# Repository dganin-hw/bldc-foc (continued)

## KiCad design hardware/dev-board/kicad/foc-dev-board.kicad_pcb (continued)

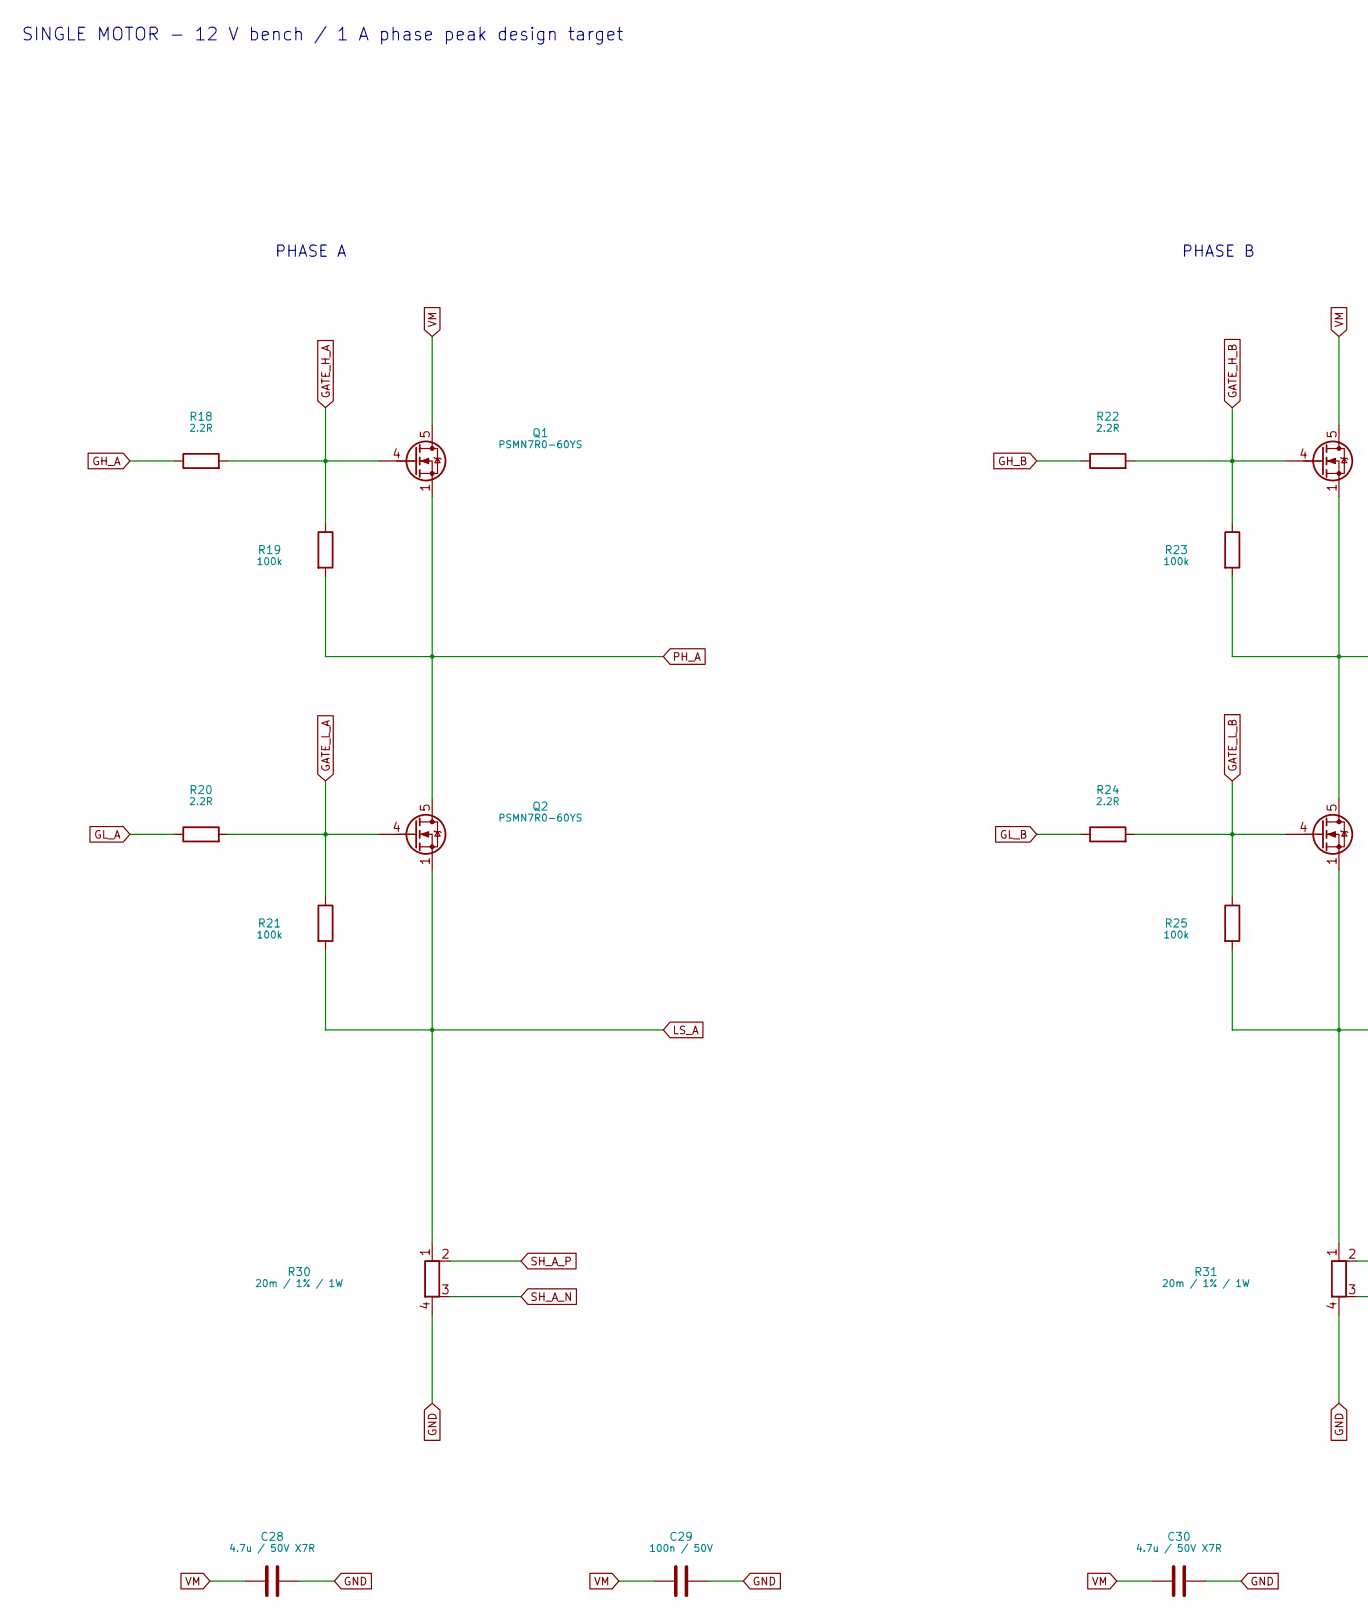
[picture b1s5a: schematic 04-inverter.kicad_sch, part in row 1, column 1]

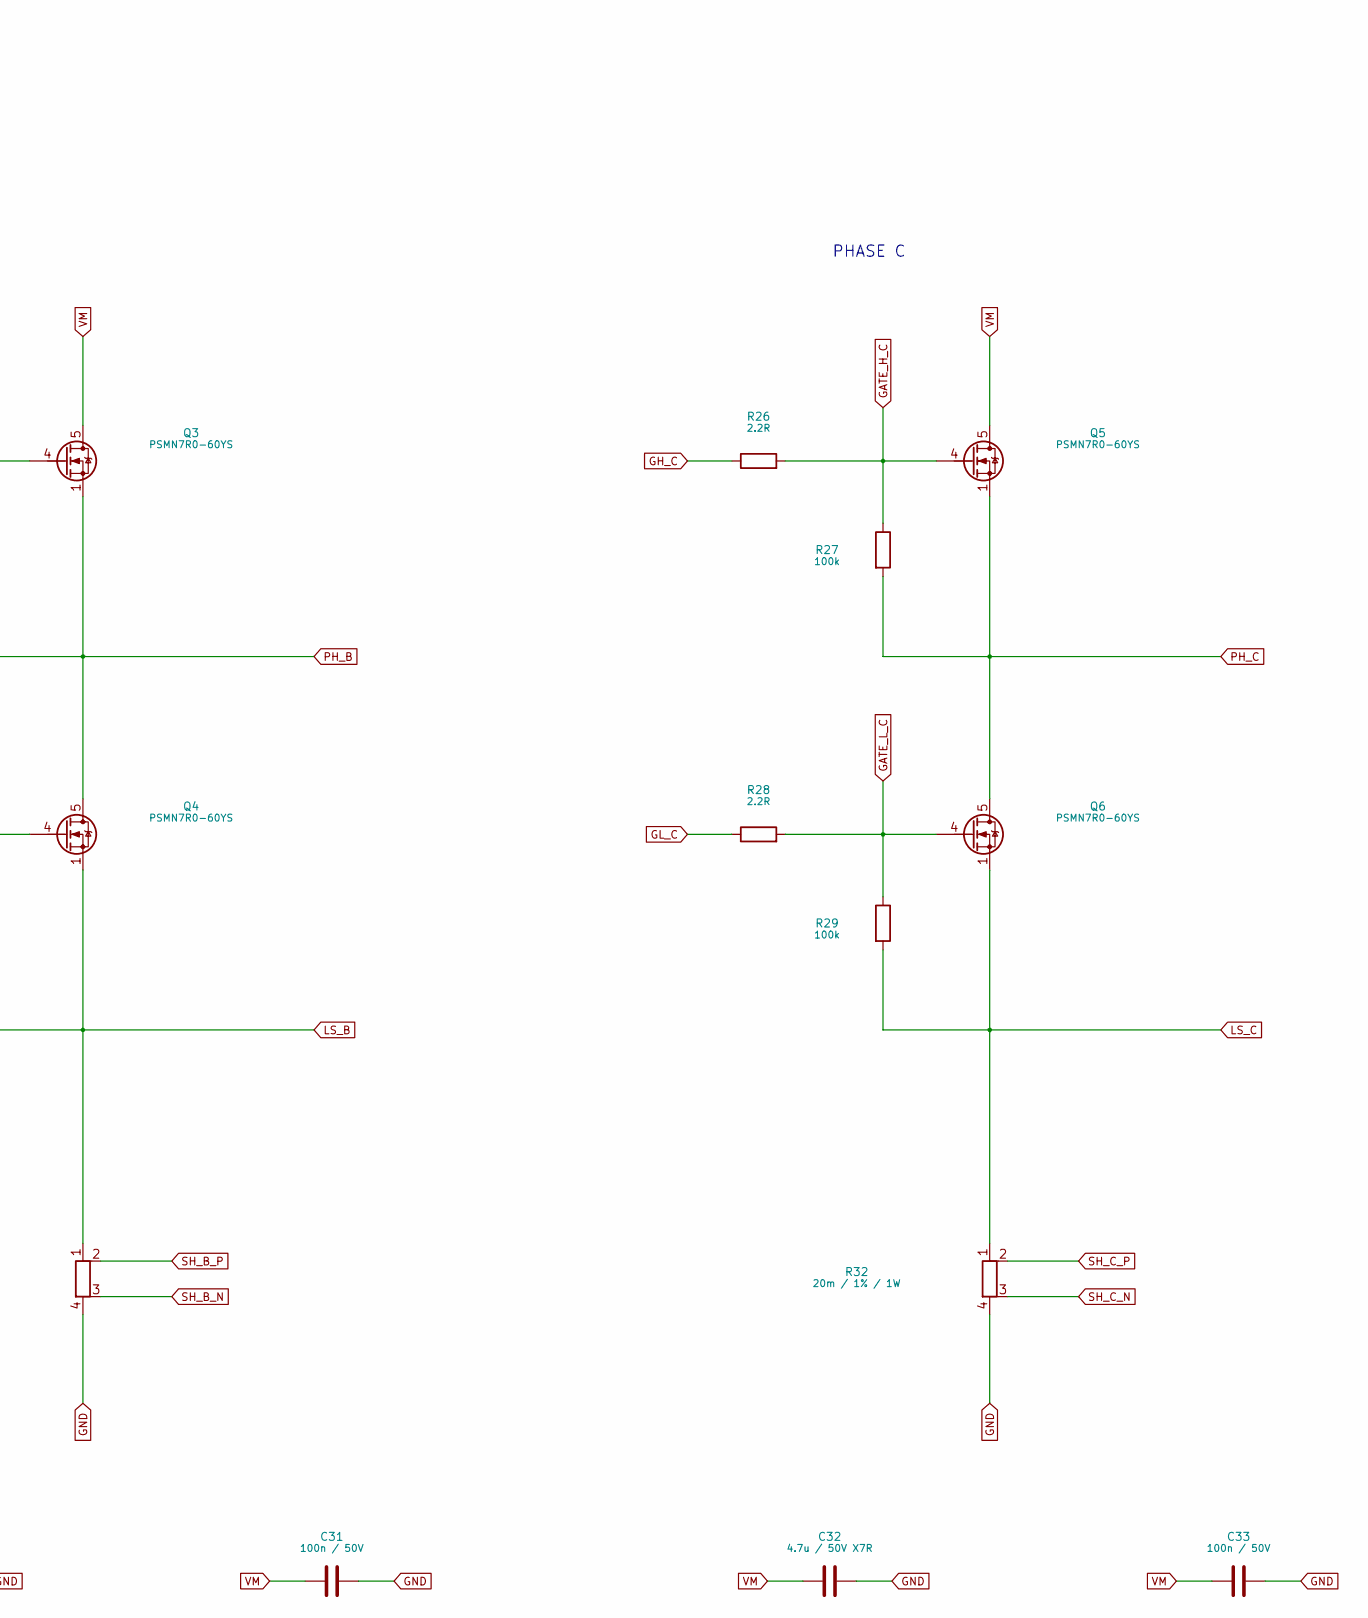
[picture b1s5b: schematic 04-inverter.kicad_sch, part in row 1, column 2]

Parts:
C28, C30, C32: 4.7u / 50V X7R; C_1210_3225Metric
C29, C31, C33: 100n / 50V; C_0603_1608Metric
Q1, Q2, Q3, Q4, Q5, Q6: PSMN7R0-60YS; LFPAK56; MPN PSMN7R0-60YS,115
R18, R20, R22, R24, R26, R28: 2.2R; R_0603_1608Metric
R19, R21, R23, R25, R27, R29: 100k; R_0603_1608Metric
R30, R31, R32: 20m / 1% / 1W; R_Shunt_Vishay_WSK2512_6332Metric_T1.19mm; MPN WSK2512R0200FEA

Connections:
GATE_H_A: Q1.4 (G), R18.2, R19.1; also elsewhere on the board
GATE_H_B: Q3.4 (G), R22.2, R23.1; also elsewhere on the board
GATE_H_C: Q5.4 (G), R26.2, R27.1; also elsewhere on the board
GATE_L_A: Q2.4 (G), R20.2, R21.1; also elsewhere on the board
GATE_L_B: Q4.4 (G), R24.2, R25.1; also elsewhere on the board
GATE_L_C: Q6.4 (G), R28.2, R29.1; also elsewhere on the board
GH_A: R18.1; also elsewhere on the board
GH_B: R22.1; also elsewhere on the board
GH_C: R26.1; also elsewhere on the board
GL_A: R20.1; also elsewhere on the board
GL_B: R24.1; also elsewhere on the board
GL_C: R28.1; also elsewhere on the board
GND: C28.2, C29.2, C30.2, C31.2, C32.2, C33.2, R30.4, R31.4, R32.4; also elsewhere on the board
LS_A: Q2.1 (S), Q2.2 (S), Q2.3 (S), R21.2, R30.1; also elsewhere on the board
LS_B: Q4.1 (S), Q4.2 (S), Q4.3 (S), R25.2, R31.1; also elsewhere on the board
LS_C: Q6.1 (S), Q6.2 (S), Q6.3 (S), R29.2, R32.1; also elsewhere on the board
PH_A: Q1.1 (S), Q1.2 (S), Q1.3 (S), Q2.5 (D), R19.2; also elsewhere on the board
PH_B: Q3.1 (S), Q3.2 (S), Q3.3 (S), Q4.5 (D), R23.2; also elsewhere on the board
PH_C: Q5.1 (S), Q5.2 (S), Q5.3 (S), Q6.5 (D), R27.2; also elsewhere on the board
SH_A_N: R30.3; also elsewhere on the board
SH_A_P: R30.2; also elsewhere on the board
SH_B_N: R31.3; also elsewhere on the board
SH_B_P: R31.2; also elsewhere on the board
SH_C_N: R32.3; also elsewhere on the board
SH_C_P: R32.2; also elsewhere on the board
VM: C28.1, C29.1, C30.1, C31.1, C32.1, C33.1, Q1.5 (D), Q3.5 (D), Q5.5 (D); also elsewhere on the board

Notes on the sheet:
PHASE B
PHASE A
SINGLE MOTOR - 12 V bench / 1 A phase peak design target
PHASE C

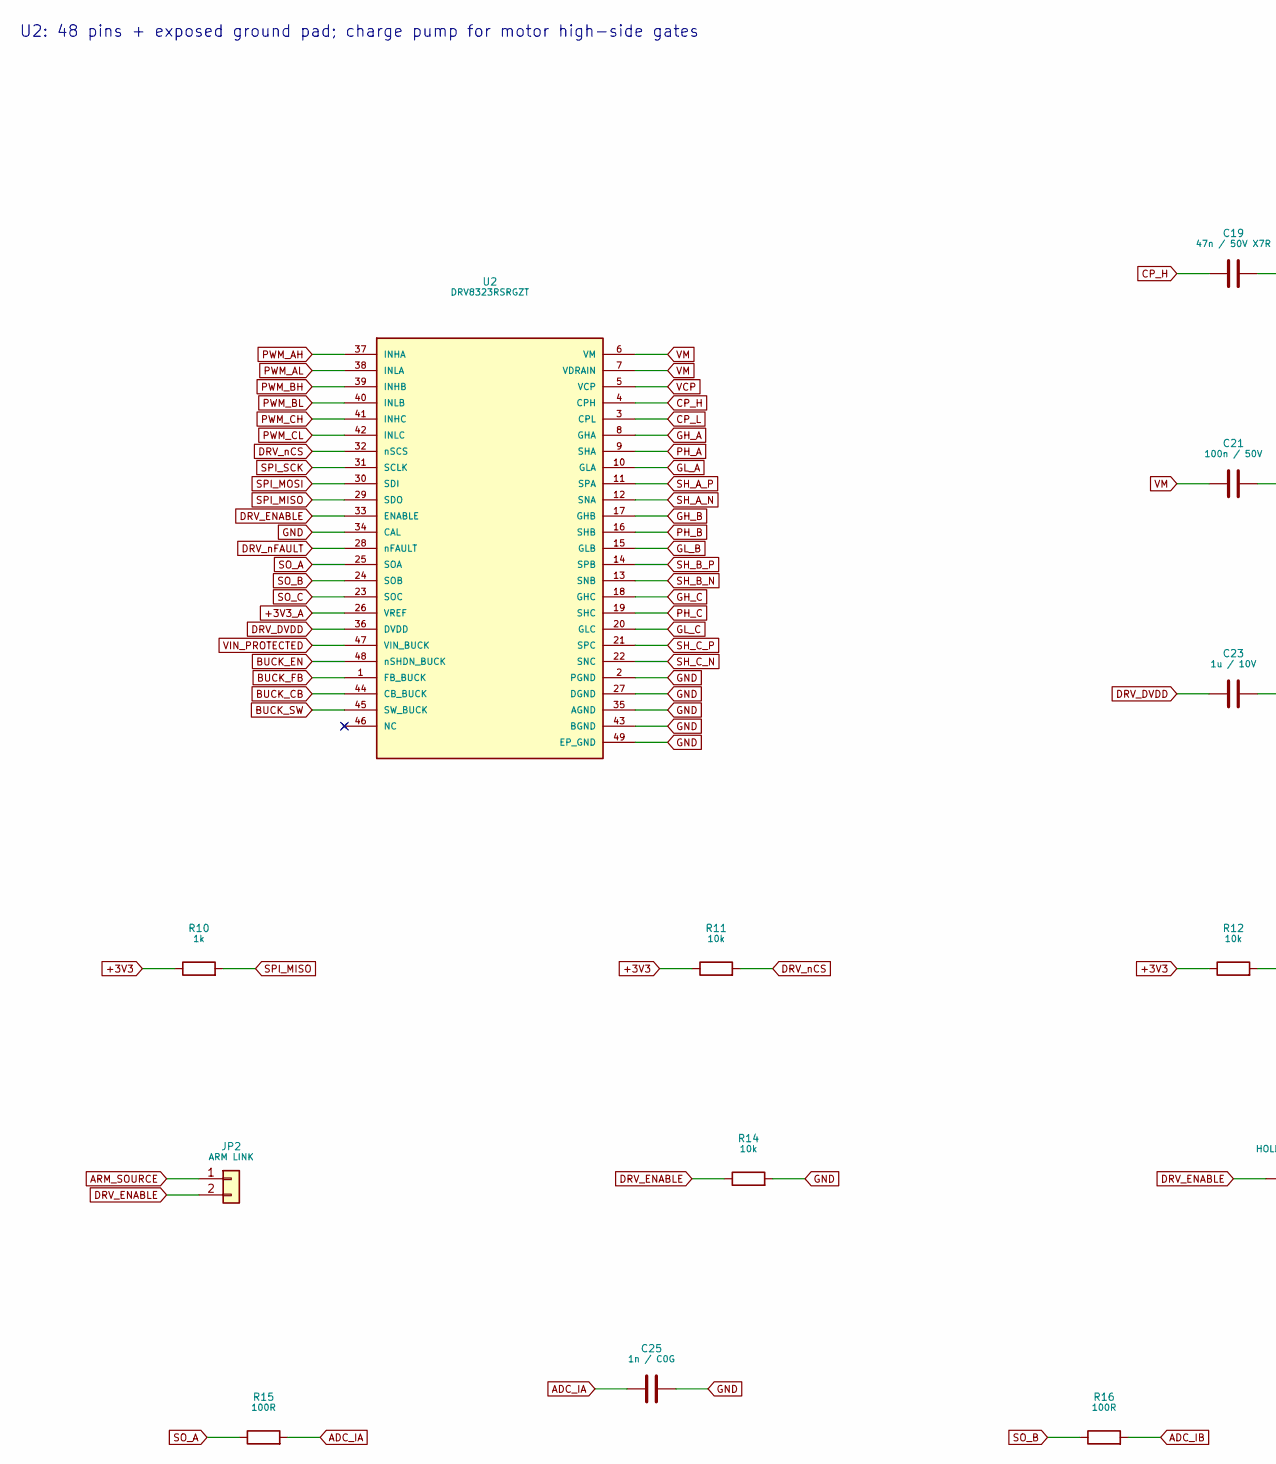
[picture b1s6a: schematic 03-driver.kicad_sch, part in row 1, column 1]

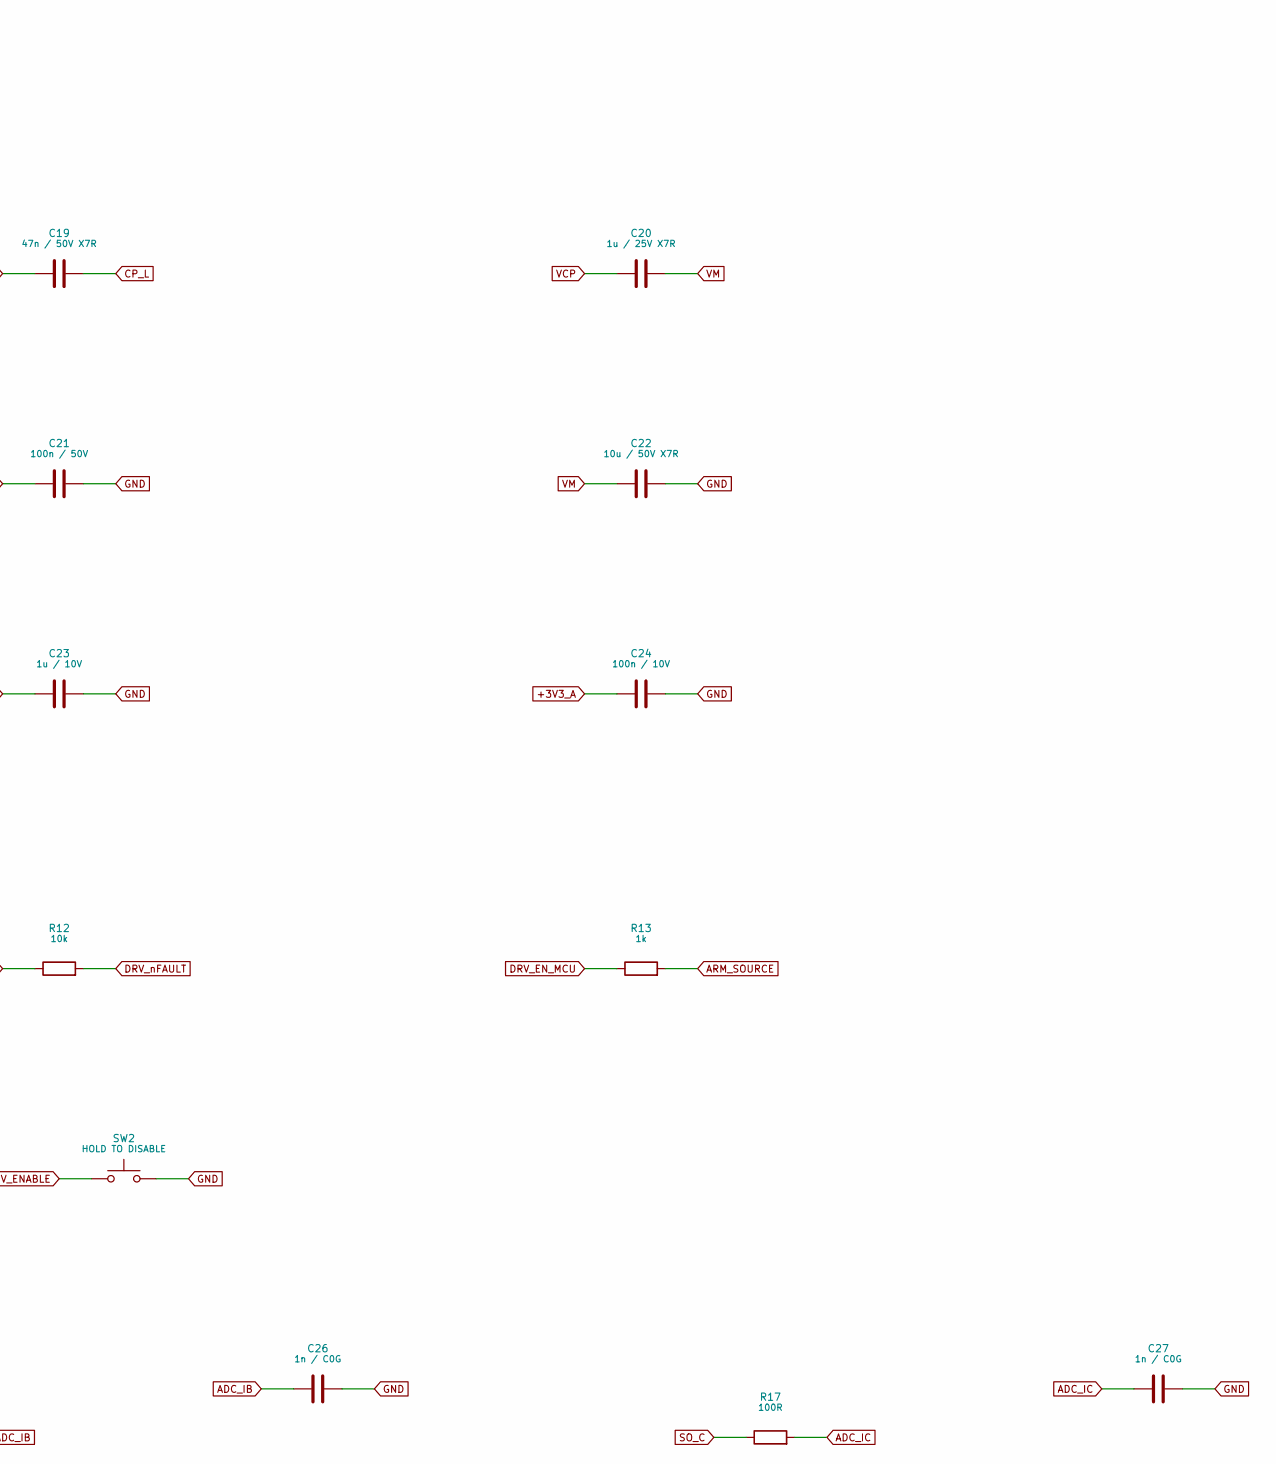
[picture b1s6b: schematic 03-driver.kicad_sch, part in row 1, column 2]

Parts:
C19: 47n / 50V X7R; C_0603_1608Metric
C20: 1u / 25V X7R; C_0805_2012Metric
C21: 100n / 50V; C_0603_1608Metric
C22: 10u / 50V X7R; C_1210_3225Metric
C23: 1u / 10V; C_0603_1608Metric
C24: 100n / 10V; C_0603_1608Metric
C25, C26, C27: 1n / C0G; C_0603_1608Metric
JP2: ARM LINK; PinHeader_1x02_P2.54mm_Vertical
R10, R13: 1k; R_0603_1608Metric
R11, R12, R14: 10k; R_0603_1608Metric
R15, R16, R17: 100R; R_0603_1608Metric
SW2: HOLD TO DISABLE; SW_SPST_TL3342; MPN TL3342F160QG
U2: DRV8323RSRGZT; Texas_RGZ0048A_VQFN-48-1EP_7x7mm_P0.5mm_EP5.15x5.15mm_Therm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; MPN DRV8323RSRGZT

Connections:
+3V3: R10.1, R11.1, R12.1; also elsewhere on the board
+3V3_A: C24.1, U2.26 (VREF); also elsewhere on the board
ADC_IA: C25.1, R15.2; also elsewhere on the board
ADC_IB: C26.1, R16.2; also elsewhere on the board
ADC_IC: C27.1, R17.2; also elsewhere on the board
ARM_SOURCE: JP2.1, R13.2
BUCK_CB: U2.44 (CB_BUCK); also elsewhere on the board
BUCK_EN: U2.48 (nSHDN_BUCK); also elsewhere on the board
BUCK_FB: U2.1 (FB_BUCK); also elsewhere on the board
BUCK_SW: U2.45 (SW_BUCK); also elsewhere on the board
CP_H: C19.1, U2.4 (CPH)
CP_L: C19.2, U2.3 (CPL)
DRV_DVDD: C23.1, U2.36 (DVDD); also elsewhere on the board
DRV_ENABLE: JP2.2, R14.1, SW2.1, U2.33 (ENABLE); also elsewhere on the board
DRV_EN_MCU: R13.1; also elsewhere on the board
DRV_nCS: R11.2, U2.32 (nSCS); also elsewhere on the board
DRV_nFAULT: R12.2, U2.28 (nFAULT); also elsewhere on the board
GH_A: U2.8 (GHA); also elsewhere on the board
GH_B: U2.17 (GHB); also elsewhere on the board
GH_C: U2.18 (GHC); also elsewhere on the board
GL_A: U2.10 (GLA); also elsewhere on the board
GL_B: U2.15 (GLB); also elsewhere on the board
GL_C: U2.20 (GLC); also elsewhere on the board
GND: C21.2, C22.2, C23.2, C24.2, C25.2, C26.2, C27.2, R14.2, SW2.2, U2.2 (PGND), U2.27 (DGND), U2.34 (CAL), U2.35 (AGND), U2.43 (BGND), U2.49 (EP_GND); also elsewhere on the board
PH_A: U2.9 (SHA); also elsewhere on the board
PH_B: U2.16 (SHB); also elsewhere on the board
PH_C: U2.19 (SHC); also elsewhere on the board
PWM_AH: U2.37 (INHA); also elsewhere on the board
PWM_AL: U2.38 (INLA); also elsewhere on the board
PWM_BH: U2.39 (INHB); also elsewhere on the board
PWM_BL: U2.40 (INLB); also elsewhere on the board
PWM_CH: U2.41 (INHC); also elsewhere on the board
PWM_CL: U2.42 (INLC); also elsewhere on the board
SH_A_N: U2.12 (SNA); also elsewhere on the board
SH_A_P: U2.11 (SPA); also elsewhere on the board
SH_B_N: U2.13 (SNB); also elsewhere on the board
SH_B_P: U2.14 (SPB); also elsewhere on the board
SH_C_N: U2.22 (SNC); also elsewhere on the board
SH_C_P: U2.21 (SPC); also elsewhere on the board
SO_A: R15.1, U2.25 (SOA)
SO_B: R16.1, U2.24 (SOB)
SO_C: R17.1, U2.23 (SOC)
SPI_MISO: R10.2, U2.29 (SDO); also elsewhere on the board
SPI_MOSI: U2.30 (SDI); also elsewhere on the board
SPI_SCK: U2.31 (SCLK); also elsewhere on the board
VCP: C20.1, U2.5 (VCP)
VIN_PROTECTED: U2.47 (VIN_BUCK); also elsewhere on the board
VM: C20.2, C21.1, C22.1, U2.6 (VM), U2.7 (VDRAIN); also elsewhere on the board

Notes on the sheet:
U2: 48 pins + exposed ground pad; charge pump for motor high-side gates

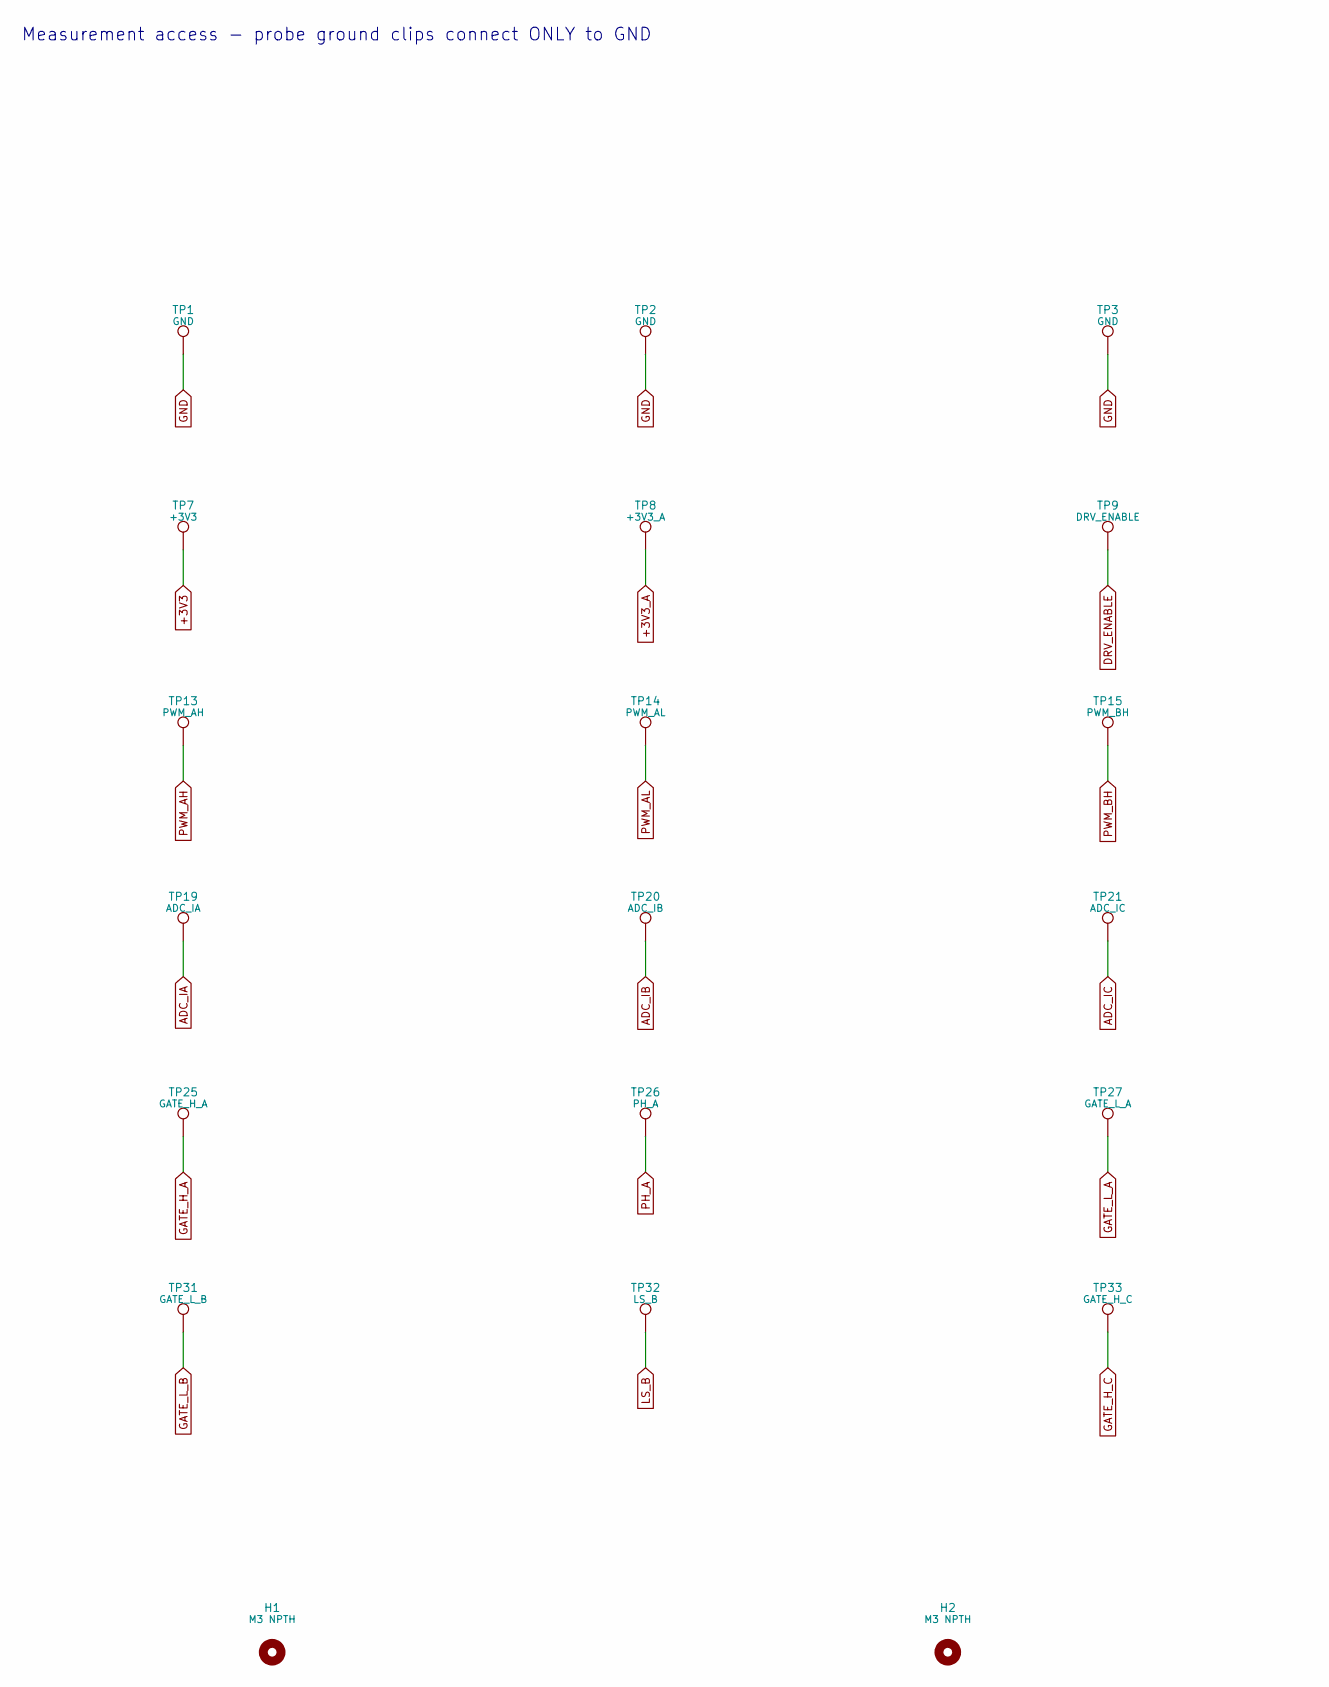
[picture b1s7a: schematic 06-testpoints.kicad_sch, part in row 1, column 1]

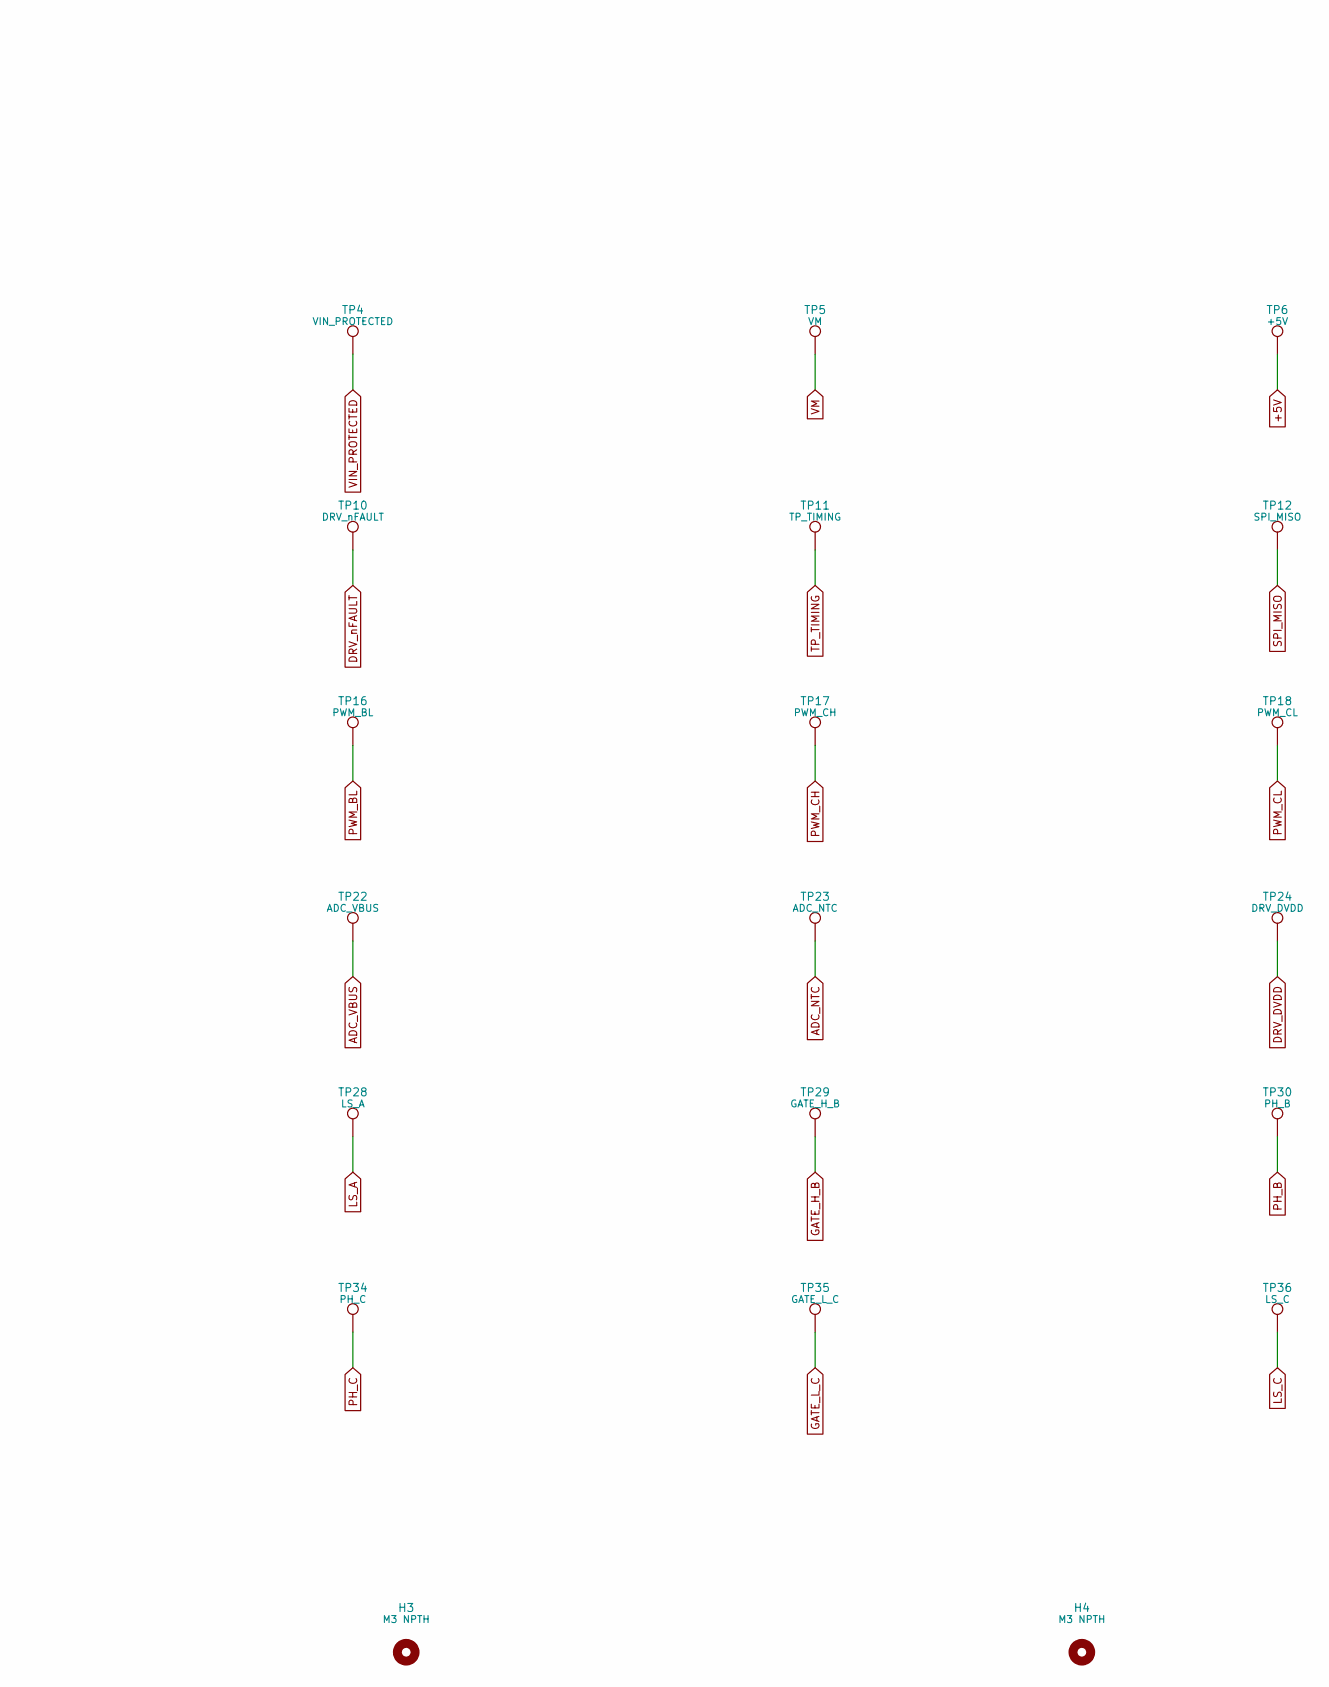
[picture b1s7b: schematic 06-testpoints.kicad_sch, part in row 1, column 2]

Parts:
H1, H2, H3, H4: M3 NPTH; MountingHole_3.2mm_M3
TP1, TP2, TP3: GND; TestPoint_Pad_D1.0mm
TP4: VIN_PROTECTED; TestPoint_Pad_D1.0mm
TP5: VM; TestPoint_Pad_D1.0mm
TP6: +5V; TestPoint_Pad_D1.0mm
TP7: +3V3; TestPoint_Pad_D1.0mm
TP8: +3V3_A; TestPoint_Pad_D1.0mm
TP9: DRV_ENABLE; TestPoint_Pad_D1.0mm
TP10: DRV_nFAULT; TestPoint_Pad_D1.0mm
TP11: TP_TIMING; TestPoint_Pad_D1.0mm
TP12: SPI_MISO; TestPoint_Pad_D1.0mm
TP13: PWM_AH; TestPoint_Pad_D1.0mm
TP14: PWM_AL; TestPoint_Pad_D1.0mm
TP15: PWM_BH; TestPoint_Pad_D1.0mm
TP16: PWM_BL; TestPoint_Pad_D1.0mm
TP17: PWM_CH; TestPoint_Pad_D1.0mm
TP18: PWM_CL; TestPoint_Pad_D1.0mm
TP19: ADC_IA; TestPoint_Pad_D1.0mm
TP20: ADC_IB; TestPoint_Pad_D1.0mm
TP21: ADC_IC; TestPoint_Pad_D1.0mm
TP22: ADC_VBUS; TestPoint_Pad_D1.0mm
TP23: ADC_NTC; TestPoint_Pad_D1.0mm
TP24: DRV_DVDD; TestPoint_Pad_D1.0mm
TP25: GATE_H_A; TestPoint_Pad_D1.0mm
TP26: PH_A; TestPoint_Pad_D1.0mm
TP27: GATE_L_A; TestPoint_Pad_D1.0mm
TP28: LS_A; TestPoint_Pad_D1.0mm
TP29: GATE_H_B; TestPoint_Pad_D1.0mm
TP30: PH_B; TestPoint_Pad_D1.0mm
TP31: GATE_L_B; TestPoint_Pad_D1.0mm
TP32: LS_B; TestPoint_Pad_D1.0mm
TP33: GATE_H_C; TestPoint_Pad_D1.0mm
TP34: PH_C; TestPoint_Pad_D1.0mm
TP35: GATE_L_C; TestPoint_Pad_D1.0mm
TP36: LS_C; TestPoint_Pad_D1.0mm

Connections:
+3V3: TP7.1; also elsewhere on the board
+3V3_A: TP8.1; also elsewhere on the board
+5V: TP6.1; also elsewhere on the board
ADC_IA: TP19.1; also elsewhere on the board
ADC_IB: TP20.1; also elsewhere on the board
ADC_IC: TP21.1; also elsewhere on the board
ADC_NTC: TP23.1; also elsewhere on the board
ADC_VBUS: TP22.1; also elsewhere on the board
DRV_DVDD: TP24.1; also elsewhere on the board
DRV_ENABLE: TP9.1; also elsewhere on the board
DRV_nFAULT: TP10.1; also elsewhere on the board
GATE_H_A: TP25.1; also elsewhere on the board
GATE_H_B: TP29.1; also elsewhere on the board
GATE_H_C: TP33.1; also elsewhere on the board
GATE_L_A: TP27.1; also elsewhere on the board
GATE_L_B: TP31.1; also elsewhere on the board
GATE_L_C: TP35.1; also elsewhere on the board
GND: TP1.1, TP2.1, TP3.1; also elsewhere on the board
LS_A: TP28.1; also elsewhere on the board
LS_B: TP32.1; also elsewhere on the board
LS_C: TP36.1; also elsewhere on the board
PH_A: TP26.1; also elsewhere on the board
PH_B: TP30.1; also elsewhere on the board
PH_C: TP34.1; also elsewhere on the board
PWM_AH: TP13.1; also elsewhere on the board
PWM_AL: TP14.1; also elsewhere on the board
PWM_BH: TP15.1; also elsewhere on the board
PWM_BL: TP16.1; also elsewhere on the board
PWM_CH: TP17.1; also elsewhere on the board
PWM_CL: TP18.1; also elsewhere on the board
SPI_MISO: TP12.1; also elsewhere on the board
TP_TIMING: TP11.1; also elsewhere on the board
VIN_PROTECTED: TP4.1; also elsewhere on the board
VM: TP5.1; also elsewhere on the board

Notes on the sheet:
Measurement access - probe ground clips connect ONLY to GND
